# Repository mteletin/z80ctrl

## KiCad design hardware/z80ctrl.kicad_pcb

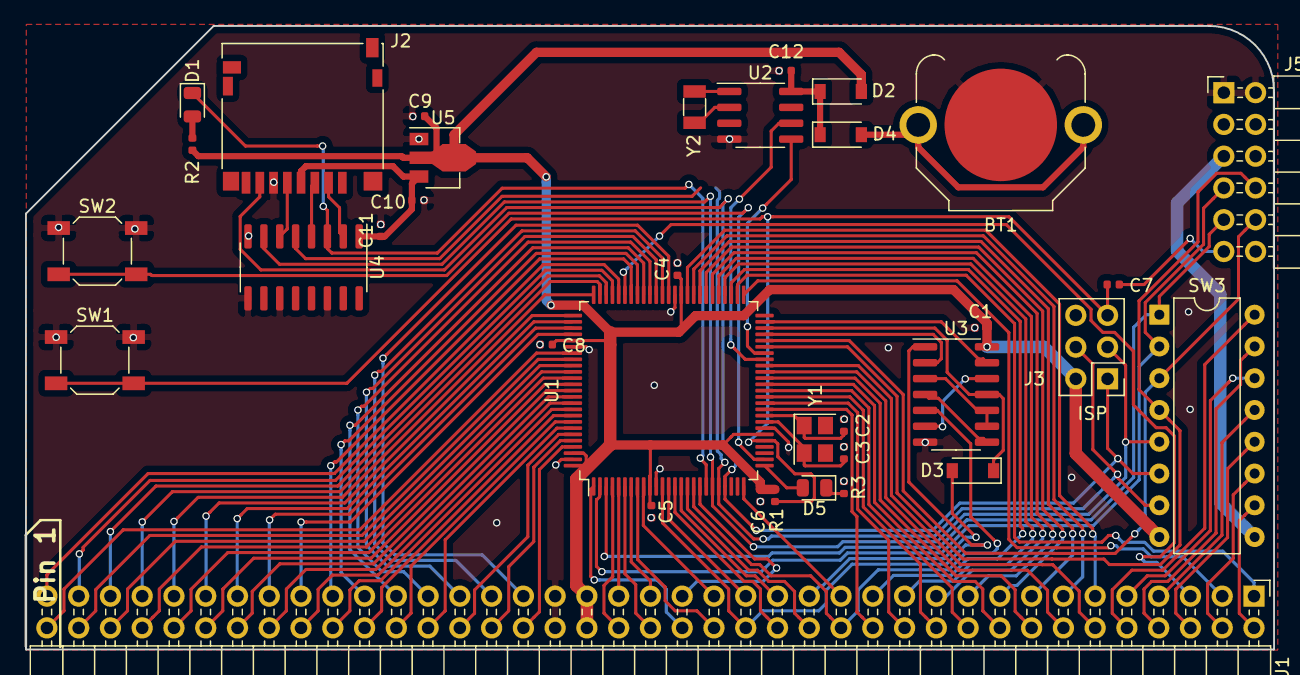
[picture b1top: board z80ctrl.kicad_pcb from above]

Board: 2 copper layers, 99.8 x 49.9 mm, 35 parts (0 on the bottom side), 109 nets.

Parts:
BT1: Battery; BatteryHolder_Keystone_3001_1x12mm
C1, C4, C5, C6, C7, C8, C11, C12: .1uf; C_0402_1005Metric
C2, C3: 18pf; C_0402_1005Metric
C9, C10: 10uf; C_0402_1005Metric
D1, D5: LED; LED_0805_2012Metric
D2, D3, D4: 1N4148W; D_SOD-123
J1: BUS; PinHeader_2x39_P2.54mm_Horizontal
J2: Micro_SD_Card; microSD_HC_Hirose_DM3D-SF
J3: ISP; PinHeader_2x03_P2.54mm_Vertical
J5: SERIAL1; PinHeader_2x06_P2.54mm_Horizontal
R1: 10K; R_0402_1005Metric
R2, R3: R; R_0402_1005Metric
SW1: RESET; SW_SPST_SKQG_WithoutStem
SW2: HALT; SW_SPST_SKQG_WithoutStem
SW3: SW_DIP_x08; DIP-16_W7.62mm
U1: ATmega2560-16AU; TQFP-100_14x14mm_P0.5mm
U2: PCF8563T; SOIC-8_3.9x4.9mm_P1.27mm
U3: 74HCT00D; SOIC-14_3.9x8.7mm_P1.27mm
U4: 4050; SOIC-16_3.9x9.9mm_P1.27mm
U5: HT75xx-1-SOT89; SOT-89-3
Y1: 20MHz; Crystal_SMD_3225-4Pin_3.2x2.5mm
Y2: 32.768kHz; Crystal_SMD_3215-2Pin_3.2x1.5mm

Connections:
/3V3: C10.1, C11.1, J2.4, U4.1, U5.3
/A0: J1.48, U1.97
/A1: J1.50, U1.96
/A2: J1.52, U1.95
/A3: J1.54, U1.94
/A4: J1.56, U1.93
/A5: J1.58, U1.92
/A6: J1.60, U1.91
/A7: J1.62, U1.90
/A8: J1.64, U1.89
/A9: J1.66, U1.88
/A10: J1.68, U1.87
/A11: J1.70, U1.86
/A12: J1.72, U1.85
/A13: J1.74, U1.84
/A14: J1.76, U1.83
/A15: J1.78, U1.82
/A16: J1.47, U1.63
/A17: J1.49, U1.64
/A18: J1.51, U1.65
/A19: J1.53, U1.66
/A20: J1.55, U1.67
/A21: J1.57, U1.68
/A22: J1.59, U1.69
/A23: J1.61, U1.79
/A24: J1.63, U1.78
/A25: J1.65, U1.77
/A26: J1.67, U1.76
/A27: J1.69, U1.75
/A28: J1.71, U1.74
/A29: J1.73, U1.73
/A30: J1.75, U1.72
/A31: J1.77, U1.71
/CLK: J1.38, U1.1
/CLK2: J1.37, U1.18
/D0: J1.26, U1.35
/D1: J1.24, U1.36
/D2: J1.22, U1.37
/D3: J1.20, U1.38
/D4: J1.18, U1.39
/D5: J1.16, U1.40
/D6: J1.14, U1.41
/D7: J1.12, U1.42
/D8: J1.25, U1.53
/D9: J1.23, U1.54
/D10: J1.21, U1.55
/D11: J1.19, U1.56
/D12: J1.17, U1.57
/D13: J1.15, U1.58
/D14: J1.13, U1.59
/D15: J1.11, U1.60
/MISO: J2.7, J3.1, SW3.6, U1.22
/MOSI: J3.4, SW3.7, U1.21, U4.5
/RX: J5.7, SW3.2, U1.2
/RX2: J5.8, SW3.4, U1.45
/RX2B: J1.7, SW3.13
/RXB: J1.8, SW3.15
/SCK: J3.3, SW3.5, U1.20, U4.7
/SCL: U1.44, U2.5
/SDA: U1.43, U2.6
/TX: J5.9, SW3.1, U1.3
/TX2: J5.10, SW3.3, U1.46
/TX2B: J1.9, SW3.14
/TXB: J1.10, SW3.16
/USER1: J1.5, U1.70
/USER2: J1.3, U1.51
/USER3: J1.1, U1.52
/USER5: J1.6, SW3.12
/USER6: J1.4, SW3.11
/USER7: J1.2, SW3.10
/VCCS: J5.5, SW3.9
/~AVRRST~: C7.2, J3.5, R1.2, SW1.2, U1.30
/~BUSACK~: J1.35, U1.9
/~BUSREQ~: J1.31, U1.15
/~HALT~: J1.33, U1.13
/~INT~: J1.36, U1.8
/~IORQ~: J1.28, U1.17, U3.5
/~M1~: J1.42, U1.4
/~MREQ~: J1.34, U1.12, U3.1
/~MWAIT~: U1.47, U3.2
/~NMI~: J1.27, U1.25
/~RD~: J1.30, U1.16
/~RFSH~: J1.41, U1.5
/~RST2~: J1.39, U1.7
/~RST~: J1.40, U1.6
/~SDCS~: D1.1, U1.19, U4.3
/~WAIT2~: D3.1, U1.48, U3.11
/~WAITCLR~: U1.49, U3.13
/~WAIT~: D3.2, J1.29
/~WR~: J1.32, U1.14
GND: BT1.2, C1.2, C2.2, C3.2, C4.2, C5.2, C6.2, C8.2, C9.2, C10.2, C11.2, C12.2, J1.45, J1.46, J2.6, J3.6, J5.1, J5.2, R3.1, SW1.1, SW2.1, U1.11, U1.32, U1.62, U1.81, U1.99, U2.4, U3.7, U4.8, U4.9, U4.11, U4.14, U5.1
unnamed: BT1.1, D4.2
unnamed: C2.1, U1.34, Y1.1
unnamed: C3.1, U1.33, Y1.2
unnamed: C7.1, J5.11
unnamed: C12.1, D2.1, D4.1, U2.8
unnamed: D1.2, R2.2
unnamed: D5.1, R3.2
unnamed: D5.2, U1.26
unnamed: J2.2, U4.2
unnamed: J2.3, U4.4
unnamed: J2.5, U4.6
unnamed: SW2.2, U1.27
unnamed: U2.1, Y2.2
unnamed: U2.2, Y2.1
unnamed: U3.4, U3.8
unnamed: U3.3, U3.9, U3.10
unnamed: U3.6, U3.12
VCC: C1.1, C4.1, C5.1, C6.1, C8.1, C9.1, D2.2, J1.43, J1.44, J3.2, R1.1, R2.1, SW3.8, U1.10, U1.31, U1.61, U1.80, U1.98, U1.100, U3.14, U5.2

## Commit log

2019-01-26 Experimental SMD stuff
2019-12-11 Updated REV5 PCB/schematics
2020-06-17 Layout ATmega2560 based SMD board

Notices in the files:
hardware/z80ctrl.kicad_pcb:
(C)2020 J.B. Langston
